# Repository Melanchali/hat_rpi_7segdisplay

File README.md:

# hat_rpi_7segdisplay
HAT Board on Raspberry Pi Model 4, 4 digit display with 8 segment

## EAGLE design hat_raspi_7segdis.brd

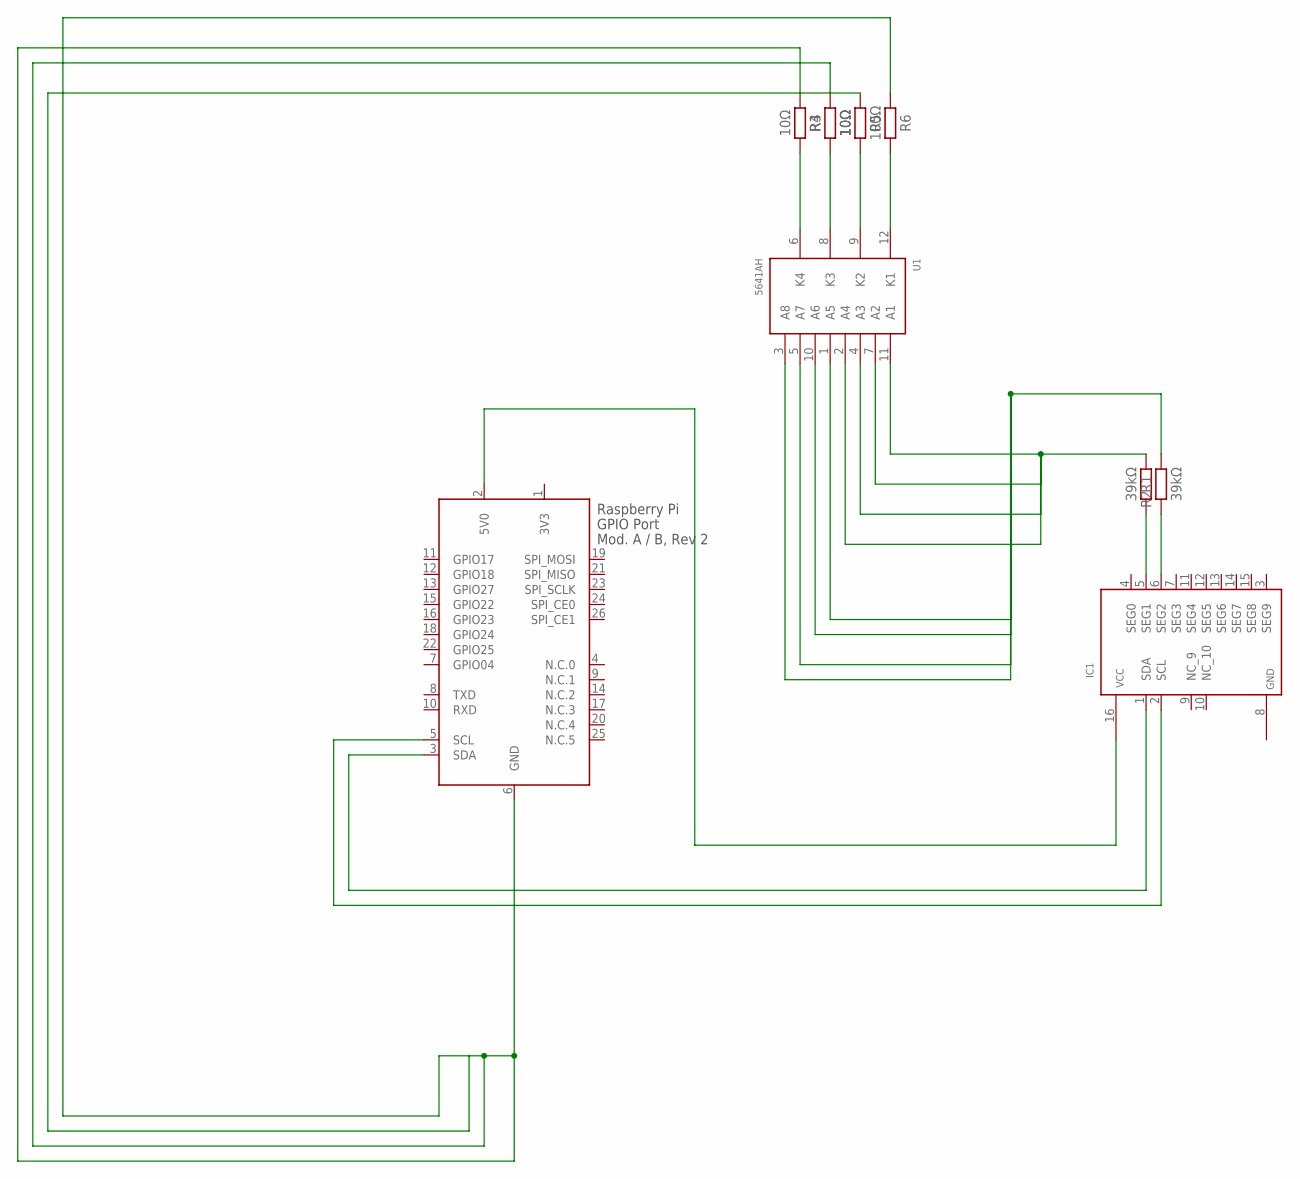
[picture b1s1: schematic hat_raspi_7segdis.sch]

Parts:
IC1: MAX6958; QSOP16
R1, R2: 39kΩ; RESAD724W46L381D178B
R3, R4, R5: 10Ω; RESAD724W46L381D178B
R6: 100Ω; RESAD724W46L381D178B
U1: 5641AH; 5642AH
X1: RASPI_BOARD_AB_E2P; RASPI_BOARD_AB_EDGES_2DRILL_PAD

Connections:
3V3: X1.1 (3V3)
GND: IC1.8 (GND)
unnamed: R4.2, U1.6 (K4)
unnamed: R3.1, U1.8 (K3)
unnamed: R5.2, U1.9 (K2)
unnamed: R6.2, U1.12 (K1)
unnamed: R3.2, R4.1, R5.1, R6.1, X1.6 (GND)
unnamed: IC1.5 (SEG1), R2.2
unnamed: IC1.6 (SEG2), R1.1
unnamed: R2.1, U1.2 (A4), U1.4 (A3), U1.7 (A2), U1.11 (A1)
unnamed: R1.2, U1.1 (A5), U1.3 (A8), U1.5 (A7), U1.10 (A6)
unnamed: IC1.2 (SCL), X1.5 (SCL)
unnamed: IC1.1 (SDA), X1.3 (SDA)
unnamed: IC1.16 (VCC), X1.2 (5V0)

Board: 2 copper layers, 9 parts (0 on the bottom side), 12 nets, no tracks yet.

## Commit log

2020-06-29 add schematik to repo
2020-07-06 Widerstände Hinfügen
2020-07-06 adding some resistors
2020-07-17 test
2020-07-18 first draft to be sent
